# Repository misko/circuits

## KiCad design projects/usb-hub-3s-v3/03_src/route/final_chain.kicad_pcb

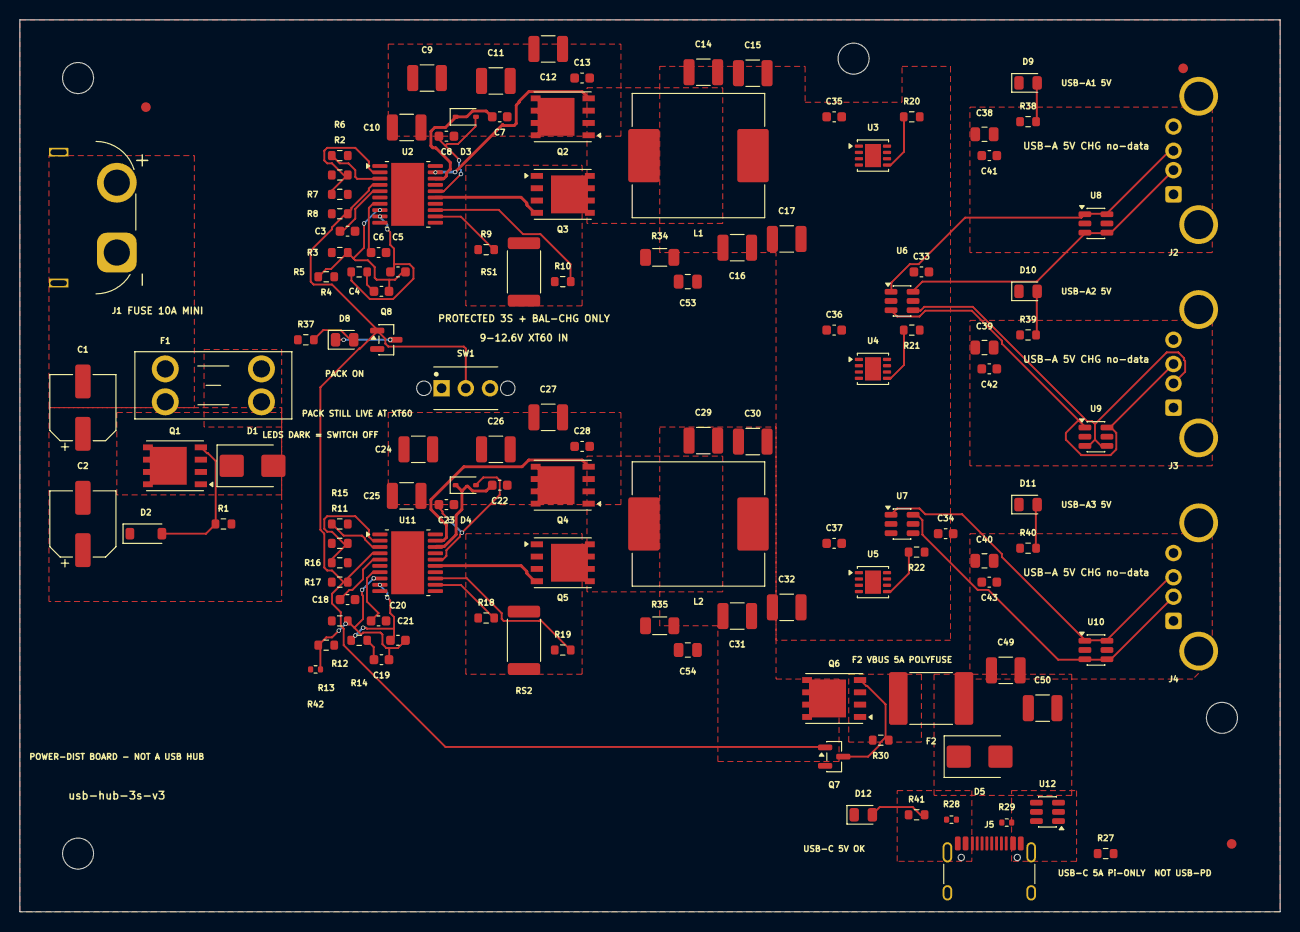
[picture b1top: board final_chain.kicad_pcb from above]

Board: 4 copper layers, 130.0 x 92.0 mm, 129 parts (0 on the bottom side), 65 nets.

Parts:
C1, C2: C2982822; CP_Elec_6.3x7.7
C3, C18: 330pF; C_0603_1608Metric
C4, C19: 3.3nF; C_0603_1608Metric
C5, C20: 100pF; C_0603_1608Metric
C6, C21: 10nF; C_0603_1608Metric
C7, C8, C22, C23: 1uF; C_0603_1608Metric
C9, C10, C11, C12, C24, C25, C26, C27, C49, C50: 10uF; C_1210_3225Metric
C13, C28, C33, C34, C35, C36, C37, C41, C42, C43: 100nF; C_0603_1608Metric
C14, C15, C16, C17, C29, C30, C31, C32: 100uF; C_1210_3225Metric
C38, C39, C40: 22uF; C_0805_2012Metric
C53, C54: 1nF; C_0805_2012Metric
D1: C83846; D_SMB
D2: C173429; D_SOD-123
D3, D4: C2128; D_SOD-323
D5: C113976; D_SMB
D8: C2296; LED_0805_2012Metric
D9, D10, D11, D12: C2297; LED_0805_2012Metric
F1: C5249699; Fuseholder_Blade_Mini_Keystone_3568
F2: C6165170; Fuse_2920_7451Metric
FID1, FID2, FID3: Fiducial_1mm_Mask2mm
H1, H2, H3, H4: MountingHole_3.2mm_M3
J1: C98732; XT60PW-M_EdgeTrim
J2, J3, J4: C503996; KH-AF90DIP-112_Horizontal
J5: C5337088; TYPE-C-31-M-12_EdgeTrim
L1, L2: C408523; L_Sunlord_MWSA1206S-6R8
Q1, Q6: C2760089; PowerPAK_SO-8_Single_Paste65
Q2, Q3, Q4, Q5: C404363; PowerPAK_SO-8_Single_Paste65
Q7, Q8: C78284; SOT-23
R1, R8, R17, R30: 100kΩ; R_0603_1608Metric
R2, R11: 12.4kΩ; R_0603_1608Metric
R3: 3.92kΩ; R_0603_1608Metric
R4, R13: 1.21kΩ; R_0603_1608Metric
R5, R14: 18kΩ; R_0603_1608Metric
R6, R15: 49.9kΩ; R_0603_1608Metric
R7, R16, R37, R38, R39, R40, R41: 6.98kΩ; R_0603_1608Metric
R9, R10, R18, R19, R27: 0Ω; R_0603_1608Metric
R12: 4.12kΩ; R_0603_1608Metric
R20, R21, R22: 36.5kΩ; R_0603_1608Metric
R28, R29: 10kΩ; R_0402_1005Metric
R34, R35: 2.2Ω; R_1206_3216Metric
R42: 160kΩ; R_0402_1005Metric
RS1, RS2: 10mΩ; R_2512_6332Metric
SW1: C2939728; SW_Slide_1P2T_CK-12D07
U2, U11: C13755; HTSSOP-20-1EP_4.4x6.5mm_P0.65mm_EP3.4x6.5mm_Mask2.75x3.43mm
U3, U4, U5: C130056; VSON-8-1EP_3x3mm_P0.65mm_EP1.65x2.4mm
U6, U7: C473910; SOT-23-6
U8, U9, U10, U12: C7519; SOT-23-6

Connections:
5VA: C14.1, C15.1, C16.1, C17.1, C33.1, C34.1, C35.1, C36.1, C37.1, L1.2, R3.1, U2.10, U3.2, U3.3, U3.4, U4.2, U4.3, U4.4, U5.2, U5.3, U5.4, U6.5, U7.5
5VC: C29.1, C30.1, C31.1, C32.1, L2.2, Q6.5, R12.1, R42.1, U11.10
BOOT_A: C7.1, D3.1, U2.18
BOOT_C: C22.1, D4.1, U11.18
CC1: J5.A5, R28.1
CC2: J5.B5, R29.1
CMZ_A: C4.1, R5.2
CMZ_C: C19.1, R14.2
COMP_A: C5.1, R5.1, U2.9
COMP_C: C20.1, R14.1, U11.9
CSF_A: R9.2, U2.12
CSF_C: R18.2, U11.12
CSGF_A: R10.2, U2.13
CSGF_C: R19.2, U11.13
CS_A: Q3.1, Q3.2, Q3.3, R9.1, RS1.1
CS_C: Q5.1, Q5.2, Q5.3, R18.1, RS2.1
DMC: J5.A7, J5.B7, R27.2, U12.3, U12.4
DM_A1: J2.2, U6.6, U8.3, U8.4
DM_A2: J3.2, U6.4, U9.3, U9.4
DM_A3: J4.2, U7.6, U10.3, U10.4
DPC: J5.A6, J5.B6, R27.1, U12.1, U12.6
DP_A1: J2.3, U6.1, U8.1, U8.6
DP_A2: J3.3, U6.3, U9.1, U9.6
DP_A3: J4.3, U7.1, U10.1, U10.6
ENKILL: Q7.1, Q8.1, R8.2, R17.2, SW1.2, U2.4, U11.4
FB_A: C4.2, C5.2, R3.2, R4.1, U2.8
FB_C: C19.2, C20.2, R12.2, R13.1, R42.2, U11.8
GND: C1.2, C2.2, C3.2, C6.2, C8.2, C9.2, C10.2, C11.2, C12.2, C13.2, C14.2, C15.2, C16.2, C17.2, C18.2, C21.2, C23.2, C24.2, C25.2, C26.2, C27.2, C28.2, C29.2, C30.2, C31.2, C32.2, C33.2, C34.2, C35.2, C36.2, C37.2, C38.2, C39.2, C40.2, C41.2, C42.2, C43.2, C49.2, C50.2, C53.2, C54.2, D1.2, D5.2, D9.1, D10.1, D11.1, D12.1, J1.1, J2.4, J2.SH, J3.4, J3.SH, J4.4, J4.SH, J5.A1, J5.A12, J5.B1, J5.B12, J5.SH, Q7.2, Q8.2, R1.2, R2.2, R4.2, R7.2, R10.1, R11.2, R13.2, R16.2, R19.1, R20.2, R21.2, R22.2, RS1.2, RS2.2, SW1.1, U2.6, U2.11, U2.14, U2.17, U2.21, U3.1, U3.9, U4.1, U4.9, U5.1, U5.9, U6.2, U7.2, U8.2, U9.2, U10.2, U11.6, U11.11, U11.14, U11.17, U11.21, U12.2
HO_A: Q2.4, U2.19
HO_C: Q4.4, U11.19
ILIM1: R20.1, U3.5
ILIM2: R21.1, U4.5
ILIM3: R22.1, U5.5
LEDPK: D8.2, R37.2
LEDPKK: D8.1, Q8.3
LEDVA1: D9.2, R38.2
LEDVA2: D10.2, R39.2
LEDVA3: D11.2, R40.2
LEDVC: D12.2, R41.2
LO_A: Q3.4, U2.15
LO_C: Q5.4, U11.15
PMID: F2.1, Q6.1, Q6.2, Q6.3, R30.1
QG: Q6.4, Q7.3, R30.2
RAMP_A: C3.1, U2.5
RAMP_C: C18.1, U11.5
RPP_G: D2.2, Q1.4, R1.1
RT_A: R2.1, U2.3
RT_C: R11.1, U11.3
SNUB_A: C53.1, R34.2
SNUB_C: C54.1, R35.2
SS_A: C6.1, U2.7
SS_C: C21.1, U11.7
SW_A: C7.2, L1.1, Q2.1, Q2.2, Q2.3, Q3.5, R34.1, U2.20
SW_C: C22.2, L2.1, Q4.1, Q4.2, Q4.3, Q5.5, R35.1, U11.20
UVLO_A: R6.2, R7.1, U2.2
UVLO_C: R15.2, R16.1, U11.2
VBAT: F1.1, J1.2
VBAT_F: F1.2, Q1.5
VBUSA1: C38.1, C41.1, J2.1, R38.1, U3.6, U3.7, U8.5
VBUSA2: C39.1, C42.1, J3.1, R39.1, U4.6, U4.7, U9.5
VBUSA3: C40.1, C43.1, J4.1, R40.1, U5.6, U5.7, U10.5
VBUSC: C49.1, C50.1, D5.1, F2.2, J5.A4, J5.A9, J5.B4, J5.B9, R28.2, R29.2, R41.1, U12.5
VCC_A: C8.1, D3.2, U2.16
VCC_C: C23.1, D4.2, U11.16
VIN: C1.1, C2.1, C9.1, C10.1, C11.1, C12.1, C13.1, C24.1, C25.1, C26.1, C27.1, C28.1, D1.1, D2.1, Q1.1, Q1.2, Q1.3, Q2.5, Q4.5, R6.1, R8.1, R15.1, R17.1, R37.1, U2.1, U11.1
